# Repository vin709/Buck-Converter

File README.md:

# ⚡ Buck-Converter
This project is a discrete and educational buck converter using popular low cost ICs and discrete components such as diodes, bjts, MOSFET, 555 timer, op-amps and comparators. It features a voltage-controlled duty cycle, an op-amp error amplifier and integrator (PI controller), discrete asynchronous high-side N-MOSFET driver and OCP/OVP protection circuit.

## Features
* Input voltage range: 6V - 40V
* Max Output power: 20 W (Design Target) 
* Topology: Asynchronous Buck Converter
* PWM Generation: 555 Timer Sawtooth + LM393 Comparator
* High-side N-MOSFET driver: BJT Totem Pole + Bootstrap Capacitor
* Voltage Regulation: LM358 Error Amplifier/Integrator
* OCP/OVP Protection (Work-in-Progress)

## How a buck converter works
A buck converter or a DC-DC stepdown converter uses **Pulse Width Modulation (PWM)** to step down the input voltage effieciently. By varying the duty cycle or the length of ON time of the square wave, the amount of power that goes into the output can be lowered. An LC low pass filter then smooths out the voltage and the high frequency signals from the switching which supplies low noise, uninterrupted voltage supply to whatever purpose it may serve.

## 🚧 Project Status & Roadmap

- [x] Discrete 555-based sawtooth generator
- [x] Comparator-based PWM generator (LM393)
- [x] High-side N-MOSFET gate drive stage
- [x] Closed-loop PI feedback control (LM358)
- [ ] Over-Current Protection (OCP) circuit
- [ ] Over-Voltage Protection (OVP) circuit

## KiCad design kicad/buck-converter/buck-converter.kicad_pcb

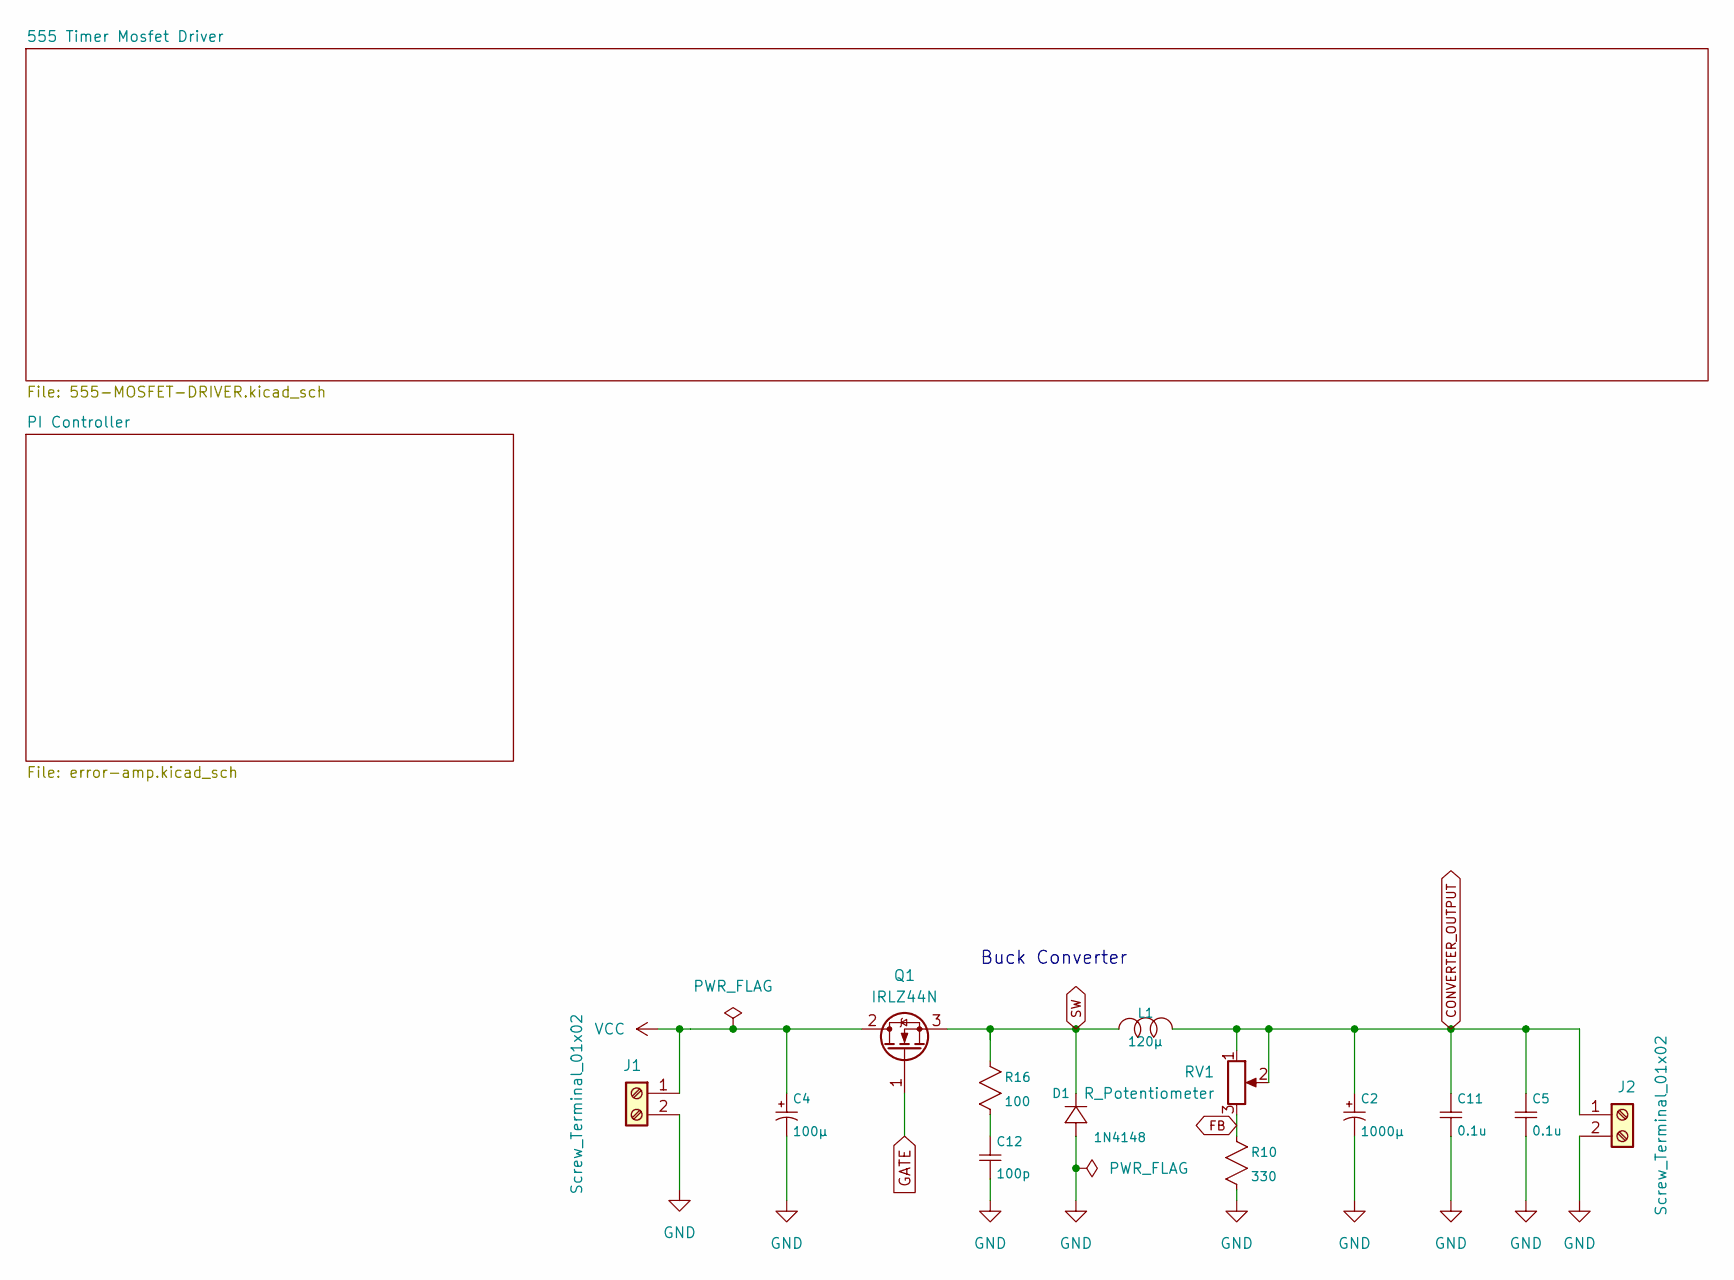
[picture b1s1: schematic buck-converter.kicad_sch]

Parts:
C2: 1000µ; C_Radial_D10.0mm_H16.0mm_P5.00mm
C4: 100µ; CP_Radial_D6.3mm_P2.50mm
C5, C11: 0.1u; C_Disc_D5.0mm_W2.5mm_P5.00mm
C12: 100p; C_Disc_D5.0mm_W2.5mm_P5.00mm
D1: 1N4148; D_DO-35_SOD27_P7.62mm_Horizontal
J1, J2: Screw_Terminal_01x02; TerminalBlock_Xinya_XY308-2.54-2P_1x02_P2.54mm_Horizontal
L1: 120µ; L_Toroid_Vertical_L10.0mm_W5.0mm_P5.08mm
Q1: IRLZ44N; TO-220-3_Vertical
R10: 330; R_Axial_DIN0204_L3.6mm_D1.6mm_P5.08mm_Horizontal
R16: 100; R_Axial_DIN0204_L3.6mm_D1.6mm_P5.08mm_Horizontal
RV1: R_Potentiometer; Potentiometer_Piher_PC-16_Single_Horizontal

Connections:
CONVERTER_OUTPUT: C2.1 (A), C5.1, C11.1, J2.1, L1.2, RV1.1, RV1.2
FB: R10.1, RV1.3; also elsewhere on the board
GATE: Q1.1 (G); also elsewhere on the board
GND: C2.2 (B), C4.2 (B), C5.2, C11.2, C12.2, D1.1 (+), J1.2, J2.2, R10.2; also elsewhere on the board
unnamed: C12.1, R16.2
SW: D1.2 (-), L1.1, Q1.3 (S), R16.1; also elsewhere on the board
VCC: C4.1 (A), J1.1, Q1.2 (D); also elsewhere on the board

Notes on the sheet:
Buck Converter

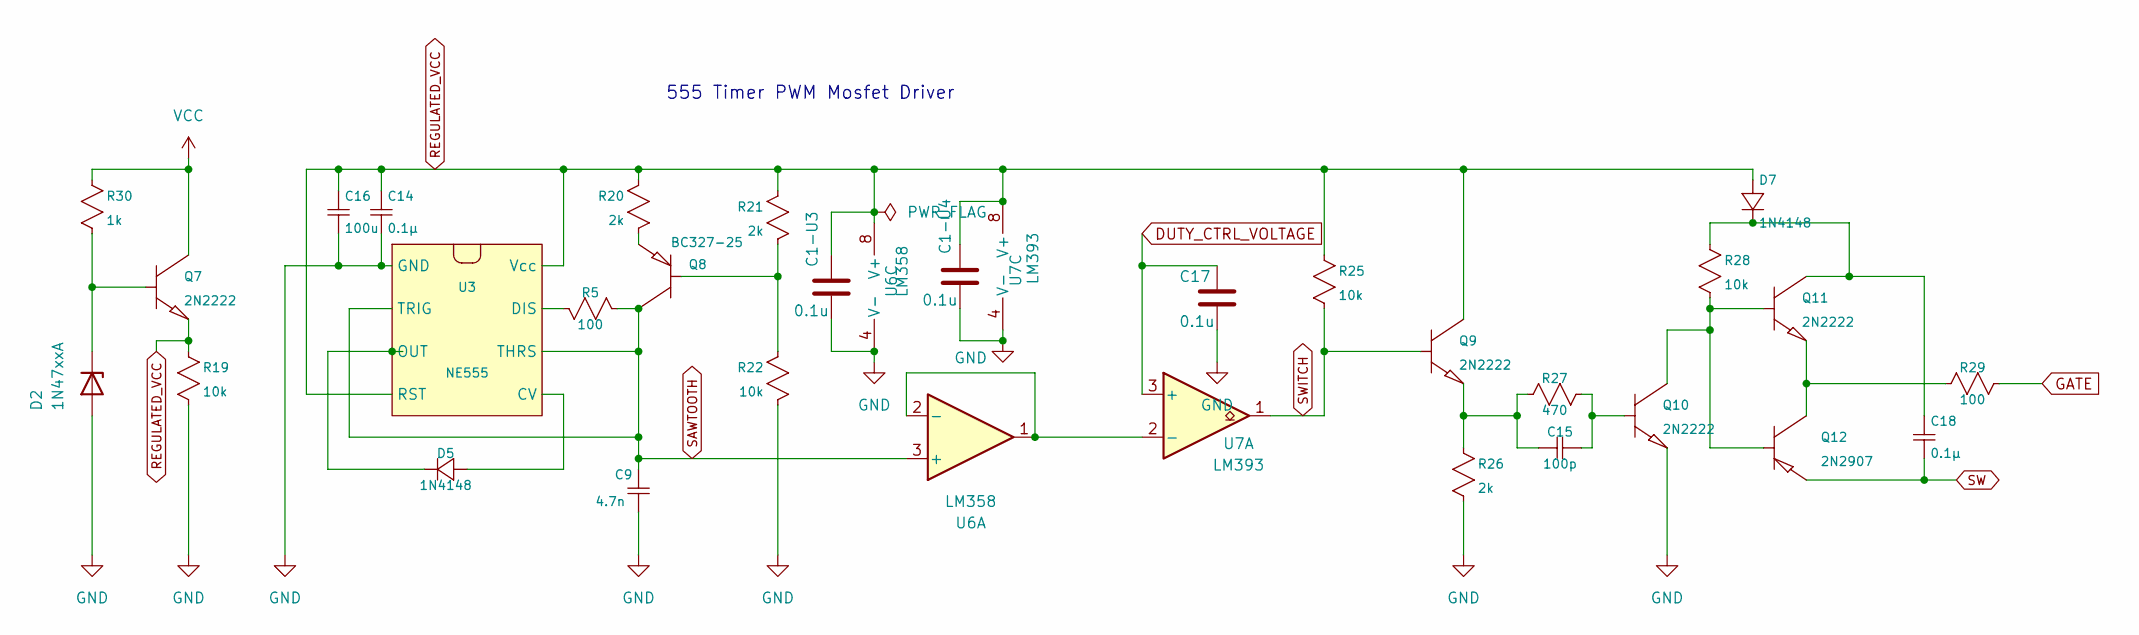
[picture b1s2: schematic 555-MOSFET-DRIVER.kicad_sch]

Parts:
C1-U3, C1-U4, C17: 0.1u; C_Disc_D5.0mm_W2.5mm_P5.00mm
C9: 4.7n; C_Disc_D5.0mm_W2.5mm_P5.00mm
C14, C18: 0.1µ; C_Disc_D5.0mm_W2.5mm_P5.00mm
C15: 100p; C_Disc_D5.0mm_W2.5mm_P5.00mm
C16: 100u; CP_Radial_D6.3mm_P2.50mm
D2: 1N47xxA; D_DO-41_SOD81_P10.16mm_Horizontal
D5, D7: 1N4148; D_DO-35_SOD27_P7.62mm_Horizontal
Q7, Q9, Q10, Q11: 2N2222; TO-92_Inline_Wide
Q8: BC327-25; TO-92_Inline_Wide
Q12: 2N2907; TO-92_Inline_Wide
R5, R29: 100; R_Axial_DIN0204_L3.6mm_D1.6mm_P5.08mm_Horizontal
R19, R22, R25, R28: 10k; R_Axial_DIN0204_L3.6mm_D1.6mm_P5.08mm_Horizontal
R20, R21, R26: 2k; R_Axial_DIN0204_L3.6mm_D1.6mm_P5.08mm_Horizontal
R27: 470; R_Axial_DIN0204_L3.6mm_D1.6mm_P5.08mm_Horizontal
R30: 1k; R_Axial_DIN0204_L3.6mm_D1.6mm_P5.08mm_Horizontal
U3: NE555; DIP-8_W7.62mm
U6: LM358; DIP-8_W7.62mm
U7: LM393; DIP-8_W7.62mm

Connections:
DUTY_CTRL_VOLTAGE: C17.1, U7.3 (+); also elsewhere on the board
GATE: R29.1; also elsewhere on the board
GND: C1-U3.2, C1-U4.2, C9.2, C14.2, C16.2, C17.2, D2.2 (A), Q10.3 (E), R19.2, R22.2, R26.2, U3.1 (GND), U6.4 (V-), U7.4 (V-); also elsewhere on the board
unnamed: D2.1 (K), Q7.2 (B), R30.2
unnamed: D5.1 (+), U3.5 (CV)
unnamed: D5.2 (-), U3.3 (OUT)
unnamed: C18.1, D7.2 (-), Q11.1 (C), R28.1
unnamed: Q8.2 (B), R21.2, R22.1
unnamed: Q8.3 (E), R20.2
unnamed: C15.2, Q9.3 (E), R26.1, R27.2
unnamed: C15.1, Q10.2 (B), R27.1
unnamed: Q10.1 (C), Q11.2 (B), Q12.2 (B), R28.2
unnamed: Q11.3 (E), Q12.1 (C), R29.2
unnamed: R5.1, U3.7 (DIS)
unnamed: U6.1, U6.2 (-), U7.2 (-)
REGULATED_VCC: C1-U3.1, C1-U4.1, C14.1, C16.1, D7.1 (+), Q7.3 (E), Q9.1 (C), R19.1, R20.1, R21.1, R25.1, U3.4 (RST), U3.8 (Vcc), U6.8 (V+), U7.8 (V+); also elsewhere on the board
SAWTOOTH: C9.1, Q8.1 (C), R5.2, U3.2 (TRIG), U3.6 (THRS), U6.3 (+)
SW: C18.2, Q12.3 (E); also elsewhere on the board
SWITCH: Q9.2 (B), R25.2, U7.1
VCC: Q7.1 (C), R30.1; also elsewhere on the board

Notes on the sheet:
555 Timer PWM Mosfet Driver

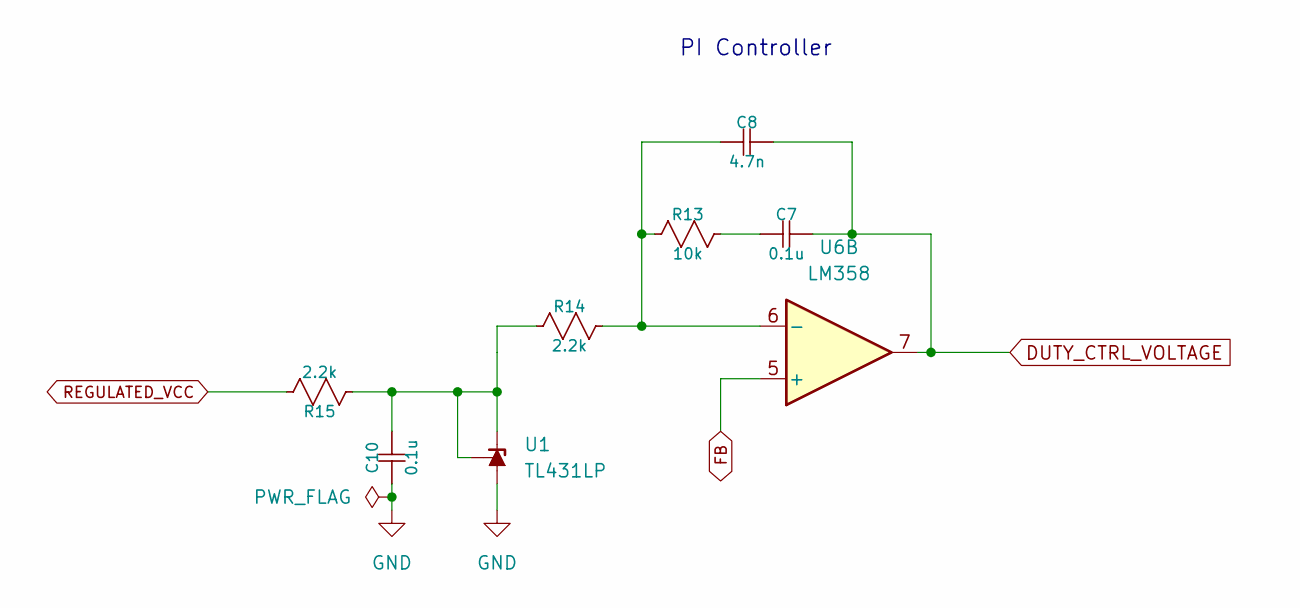
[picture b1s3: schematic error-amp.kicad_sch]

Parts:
C7, C10: 0.1u; C_Disc_D5.0mm_W2.5mm_P5.00mm
C8: 4.7n; C_Disc_D5.0mm_W2.5mm_P5.00mm
R13: 10k; R_Axial_DIN0204_L3.6mm_D1.6mm_P5.08mm_Horizontal
R14, R15: 2.2k; R_Axial_DIN0204_L3.6mm_D1.6mm_P5.08mm_Horizontal
U1: TL431LP; TO-92_Inline_Wide
U6: LM358; DIP-8_W7.62mm

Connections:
DUTY_CTRL_VOLTAGE: C7.1, C8.1, U6.7; also elsewhere on the board
FB: U6.5 (+); also elsewhere on the board
GND: C10.2, U1.2 (A); also elsewhere on the board
unnamed: C7.2, R13.1
unnamed: C10.1, R14.2, R15.2, U1.1 (REF), U1.3 (K)
unnamed: C8.2, R13.2, R14.1, U6.6 (-)
REGULATED_VCC: R15.1; also elsewhere on the board

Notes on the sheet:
PI Controller

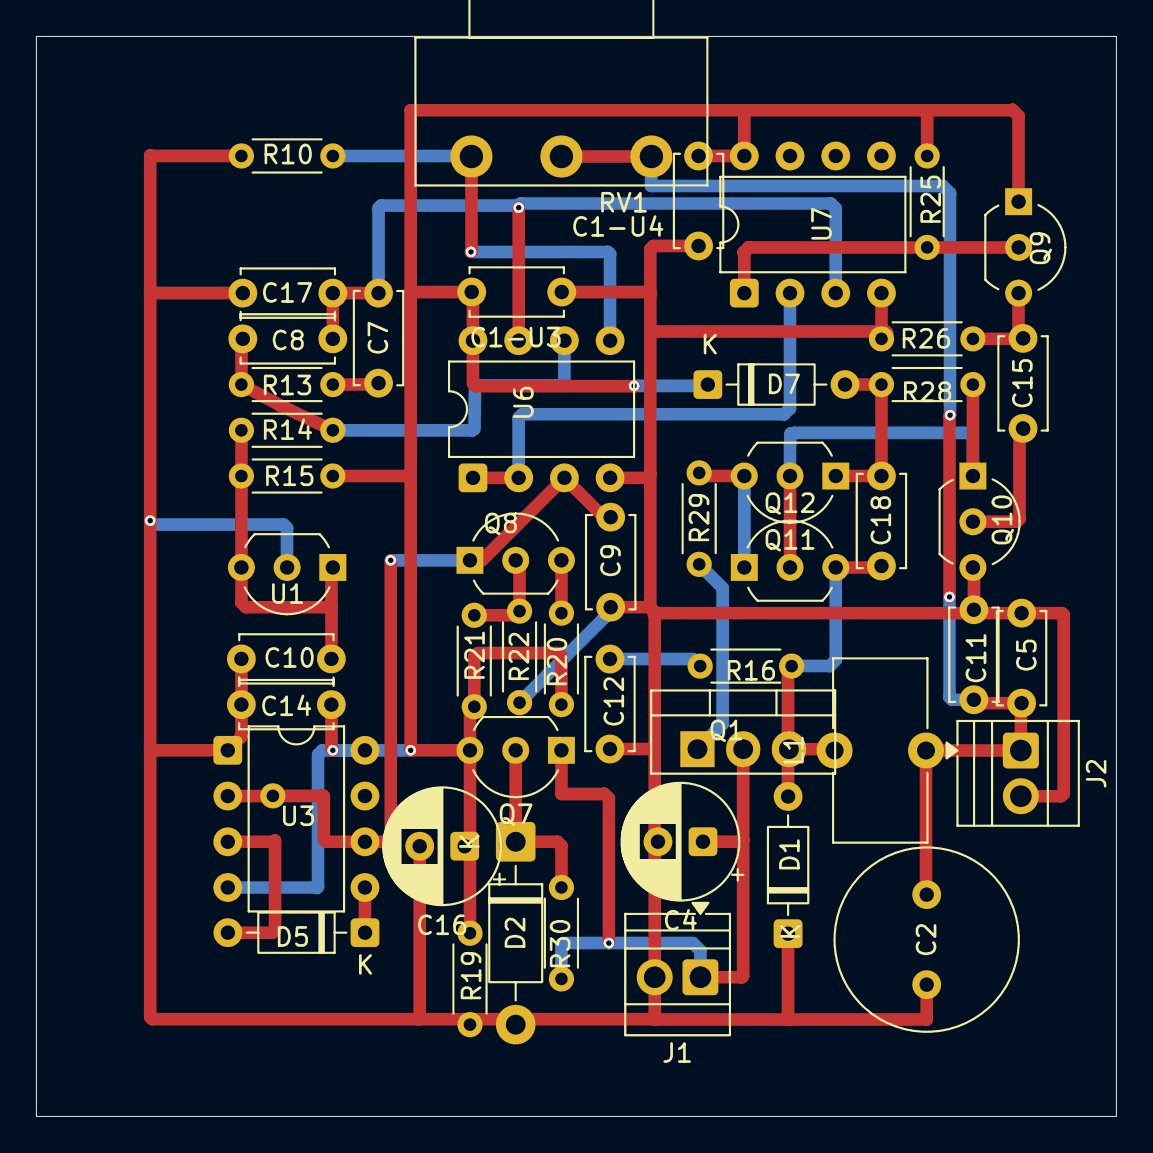
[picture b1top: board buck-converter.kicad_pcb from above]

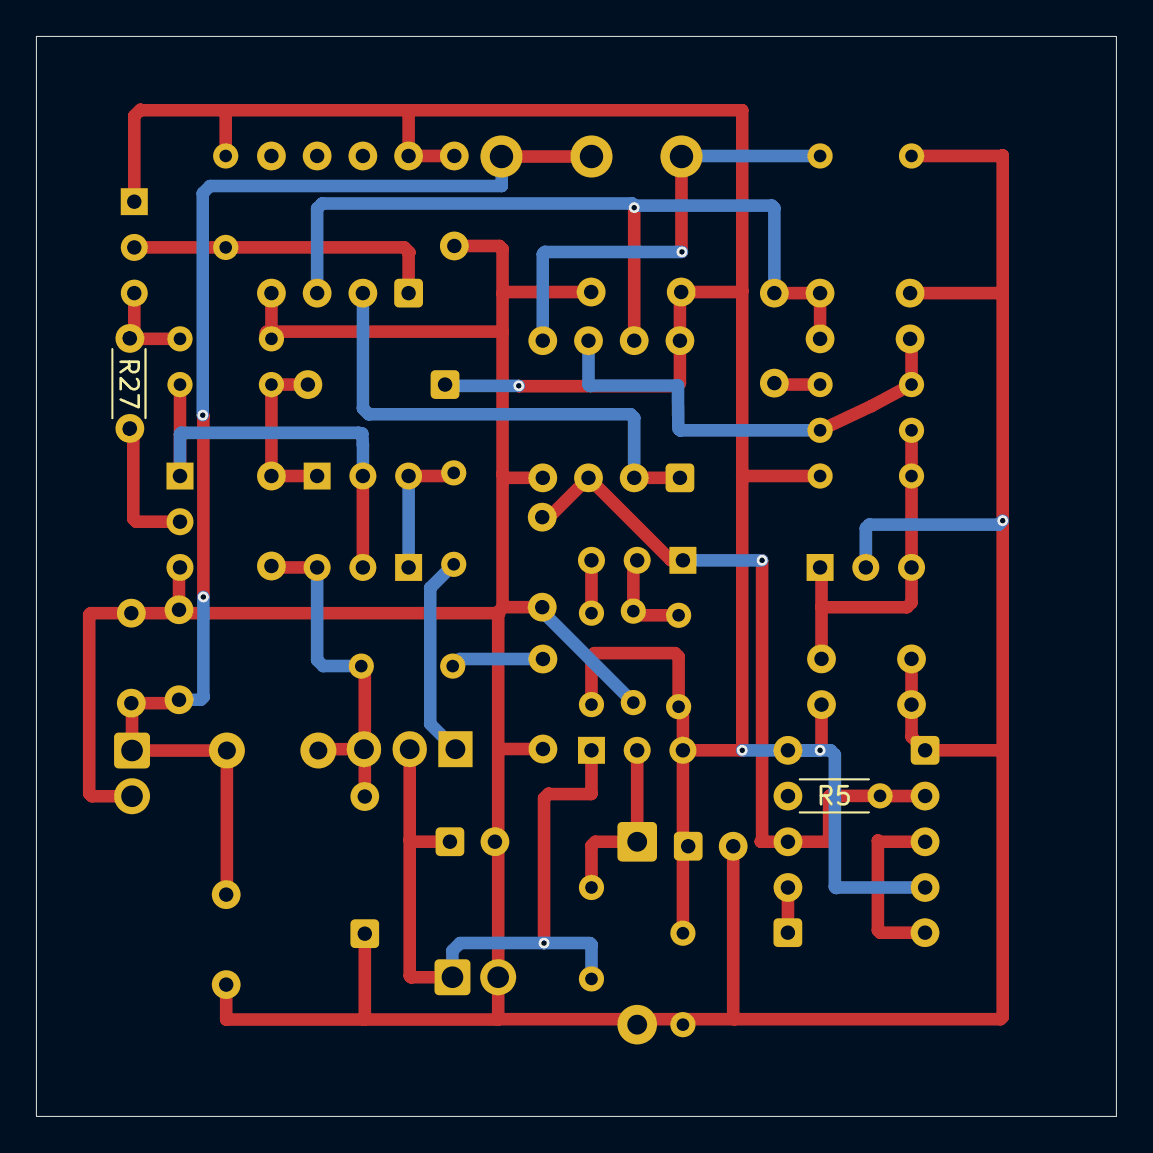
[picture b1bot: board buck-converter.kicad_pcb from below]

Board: 2 copper layers, 60.0 x 60.0 mm, 51 parts (2 on the bottom side), 26 nets.
